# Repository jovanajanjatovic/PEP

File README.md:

## Set štampanih ploča namenjenih za učenje elektronike

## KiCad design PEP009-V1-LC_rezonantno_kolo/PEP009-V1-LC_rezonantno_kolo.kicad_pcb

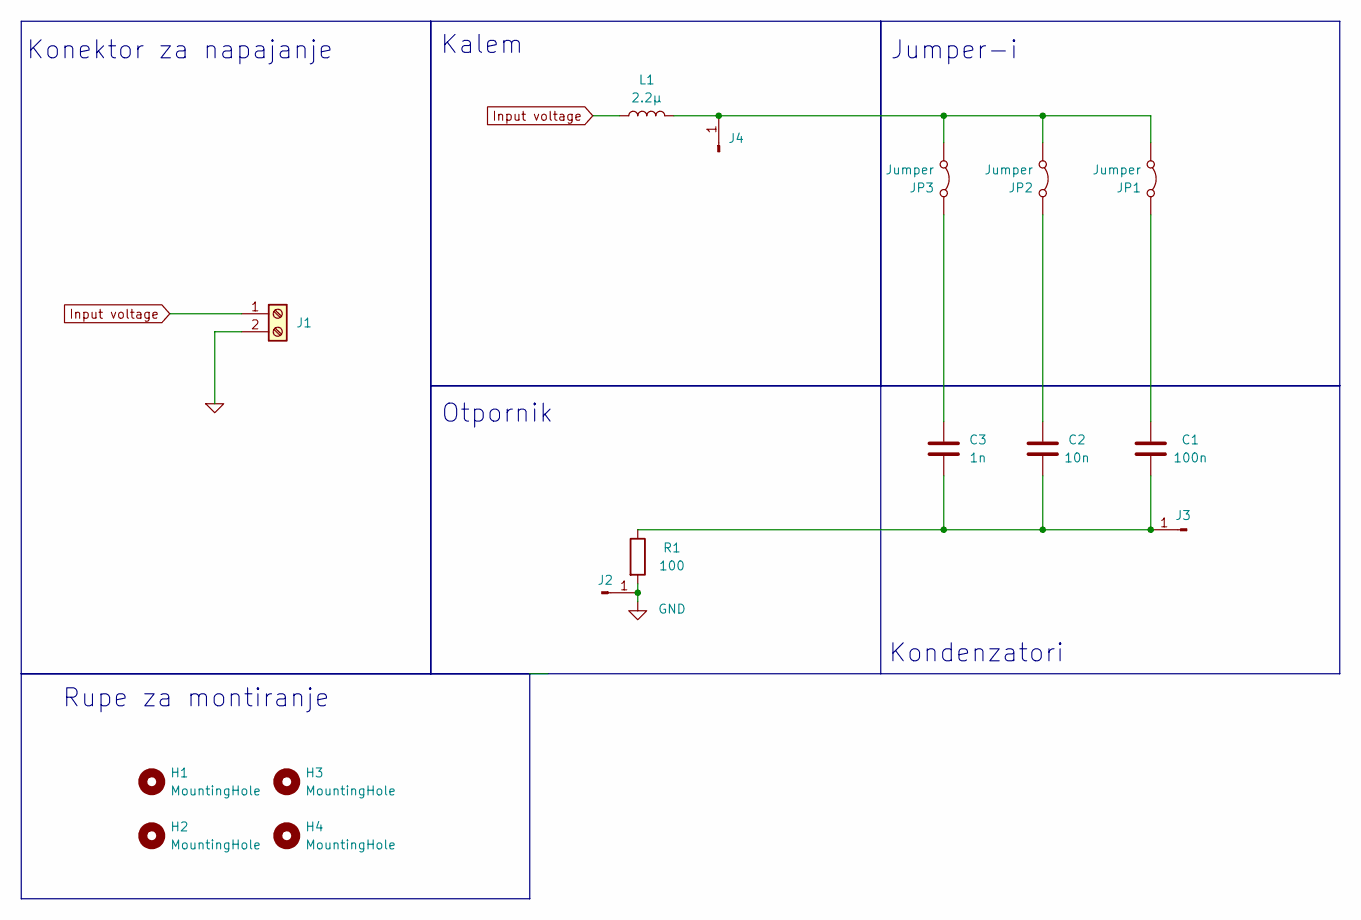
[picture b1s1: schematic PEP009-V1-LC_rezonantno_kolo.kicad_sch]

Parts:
C1: 100n; C_1206_3216Metric; LCSC C24497
C2: 10n; C_1206_3216Metric; LCSC C1846
C3: 1n; C_1206_3216Metric; LCSC C9196
H1, H2, H3, H4: MountingHole; MountingHole_3.2mm_M3_ISO14580_Pad_TopBottom
J1: Screw_Terminal_01x02; TerminalBlock_Phoenix_MKDS-1,5-2-5.08_1x02_P5.08mm_Horizont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
J2, J3, J4: Conn_01x01_Pin; PinHeader_1x01_P2.54mm_Vertical
JP1, JP2, JP3: Jumper; PinHeader_1x02_P2.54mm_Vertical
L1: 2.2µ; L_0805_2012Metric; LCSC C55755
R1: 100; R_smd; LCSC C17901

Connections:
0: J1.2
GND: J2.1, R1.2
Input voltage: J1.1, L1.1
unnamed: C1.2, C2.2, C3.2, J3.1, R1.1
unnamed: J4.1, JP1.1 (A), JP2.1 (A), JP3.1 (A), L1.2
unnamed: C1.1, JP1.2 (B)
unnamed: C2.1, JP2.2 (B)
unnamed: C3.1, JP3.2 (B)

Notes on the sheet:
Kondenzatori
Otpornik
Rupe za montiranje
Kalem
Konektor za napajanje
Jumper-i

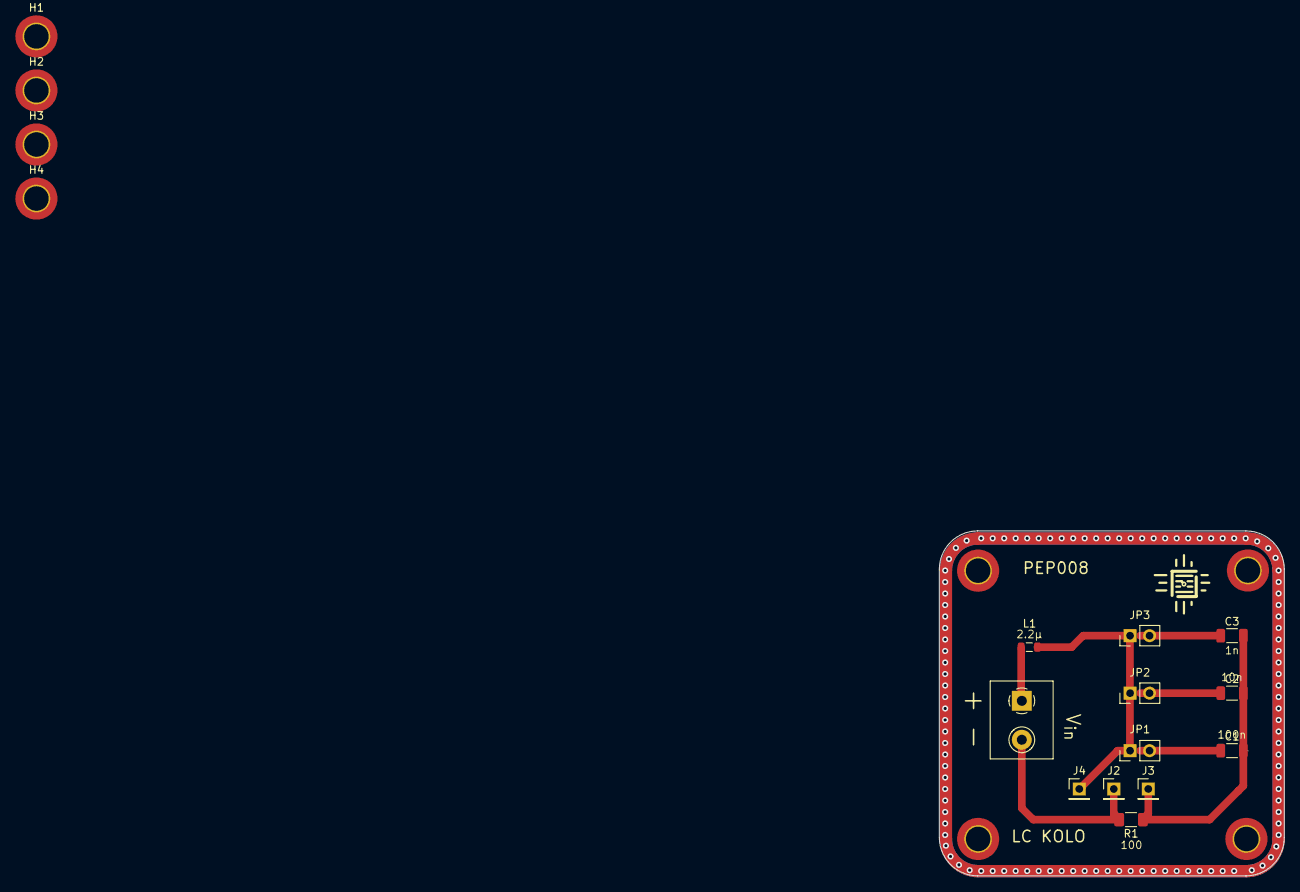
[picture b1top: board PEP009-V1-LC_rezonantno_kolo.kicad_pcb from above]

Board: 2 copper layers, 45.0 x 45.0 mm, 20 parts (0 on the bottom side), 7 nets.

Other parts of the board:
H1#2, H2#2, H3#2, H4#2: MountingHole; MountingHole_3.2mm_M3_ISO14580_Pad_TopBottom

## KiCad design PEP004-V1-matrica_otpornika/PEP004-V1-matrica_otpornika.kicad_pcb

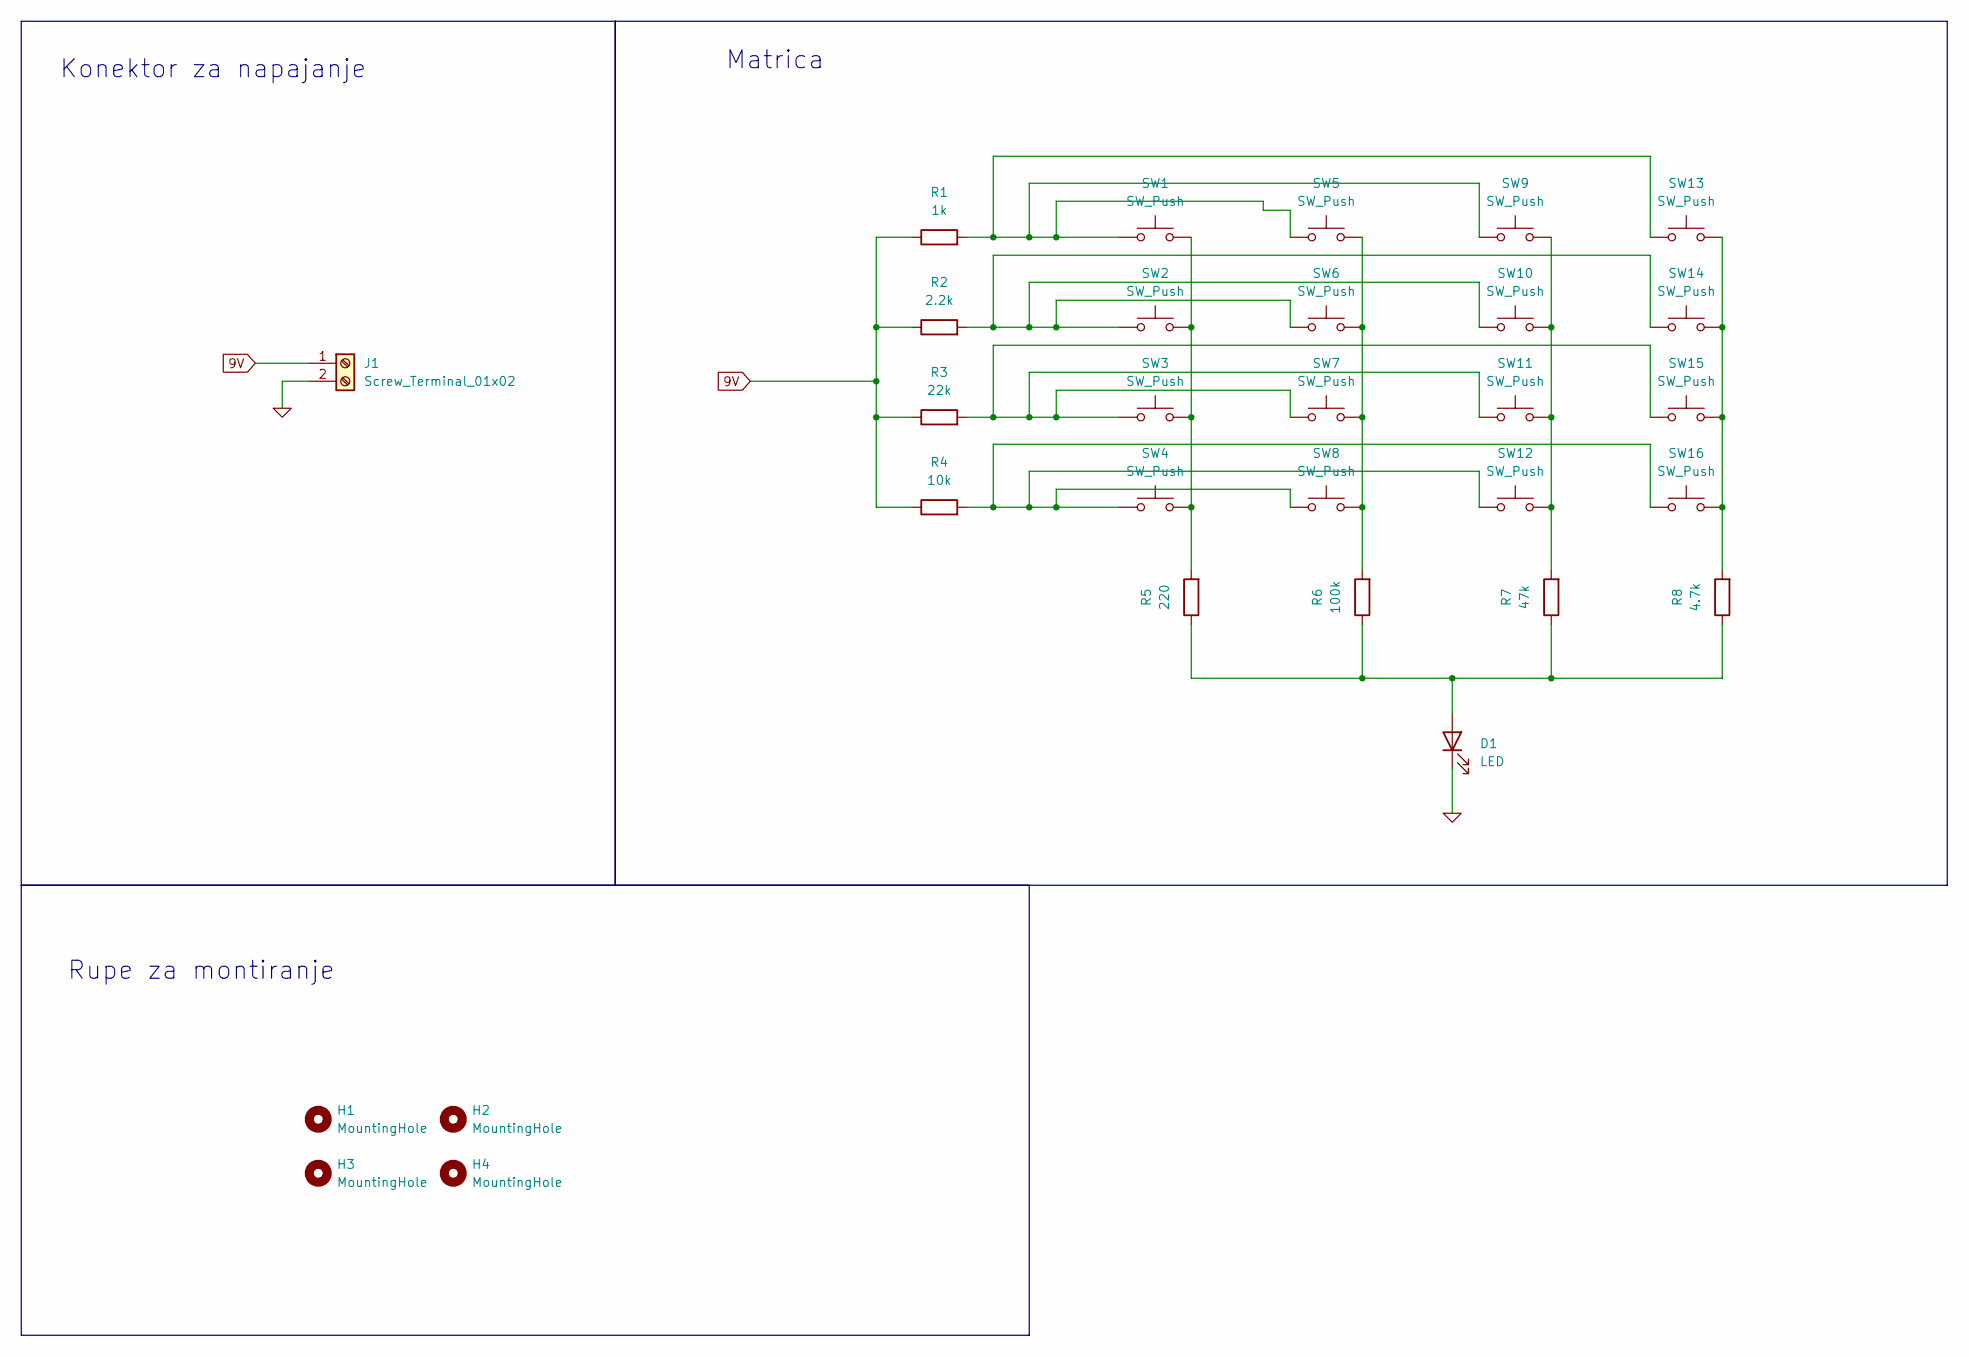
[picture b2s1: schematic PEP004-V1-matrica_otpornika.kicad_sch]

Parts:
D1: LED; LED_1206_3216Metric_Pad1.42x1.75mm_HandSolder
H1, H2, H3, H4: MountingHole; MountingHole_3.2mm_M3_ISO14580_Pad_TopBottom
J1: Screw_Terminal_01x02; TerminalBlock_Phoenix_MKDS-1,5-2-5.08_1x02_P5.08mm_Horizont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
R1: 1k; R_1206_3216Metric_Pad1.30x1.75mm_HandSolder
R2: 2.2k; R_1206_3216Metric_Pad1.30x1.75mm_HandSolder
R3: 22k; R_1206_3216Metric_Pad1.30x1.75mm_HandSolder
R4: 10k; R_1206_3216Metric_Pad1.30x1.75mm_HandSolder
R5: 220; R_1206_3216Metric_Pad1.30x1.75mm_HandSolder
R6: 100k; R_1206_3216Metric_Pad1.30x1.75mm_HandSolder
R7: 47k; R_1206_3216Metric_Pad1.30x1.75mm_HandSolder
R8: 4.7k; R_1206_3216Metric_Pad1.30x1.75mm_HandSolder
SW1, SW2, SW3, SW4, SW5, SW6, SW7, SW8, SW9, SW10, SW11, SW12, SW13, SW14, SW15, SW16: SW_Push; SW_PUSH_6mm_H4.3mm

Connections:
0: D1.1 (K), J1.2
9V: J1.1, R1.1, R2.1, R3.1, R4.1
unnamed: D1.2 (A), R5.1, R6.1, R7.1, R8.1
unnamed: R1.2, SW1.1, SW5.1, SW9.1, SW13.1
unnamed: R2.2, SW2.1, SW6.1, SW10.1, SW14.1
unnamed: R3.2, SW3.1, SW7.1, SW11.1, SW15.1
unnamed: R4.2, SW4.1, SW8.1, SW12.1, SW16.1
unnamed: R5.2, SW1.2, SW2.2, SW3.2, SW4.2
unnamed: R6.2, SW5.2, SW6.2, SW7.2, SW8.2
unnamed: R7.2, SW9.2, SW10.2, SW11.2, SW12.2
unnamed: R8.2, SW13.2, SW14.2, SW15.2, SW16.2

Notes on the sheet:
Rupe za montiranje
Konektor za napajanje
Matrica

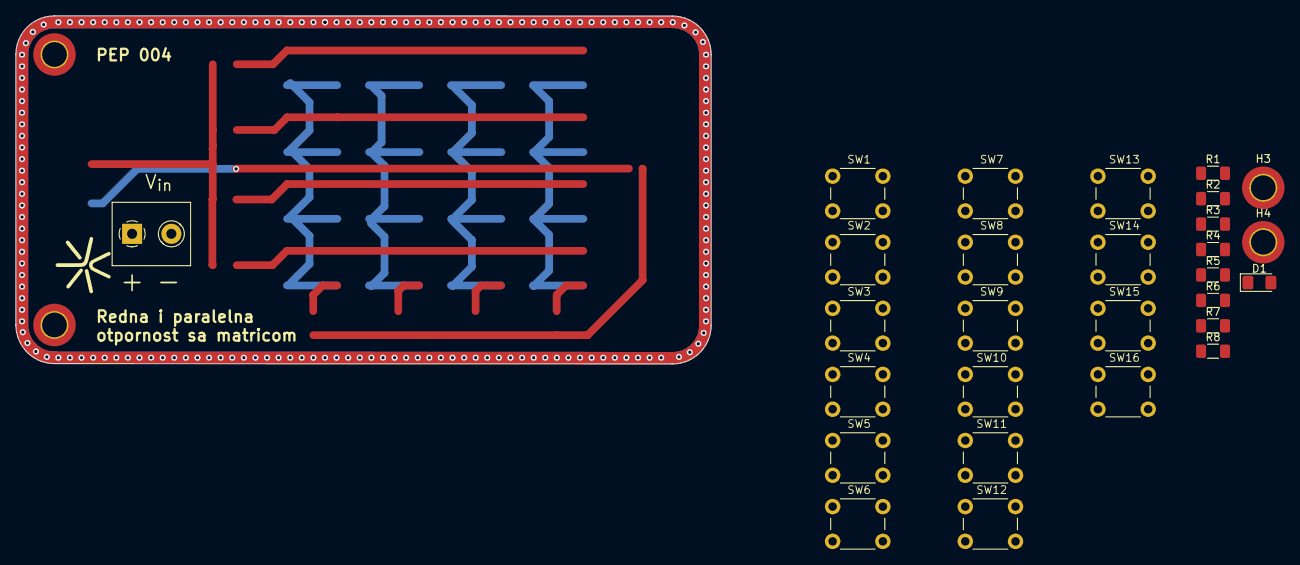
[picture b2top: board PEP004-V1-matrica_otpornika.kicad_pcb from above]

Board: 2 copper layers, 90.0 x 45.0 mm, 30 parts (0 on the bottom side), 11 nets.

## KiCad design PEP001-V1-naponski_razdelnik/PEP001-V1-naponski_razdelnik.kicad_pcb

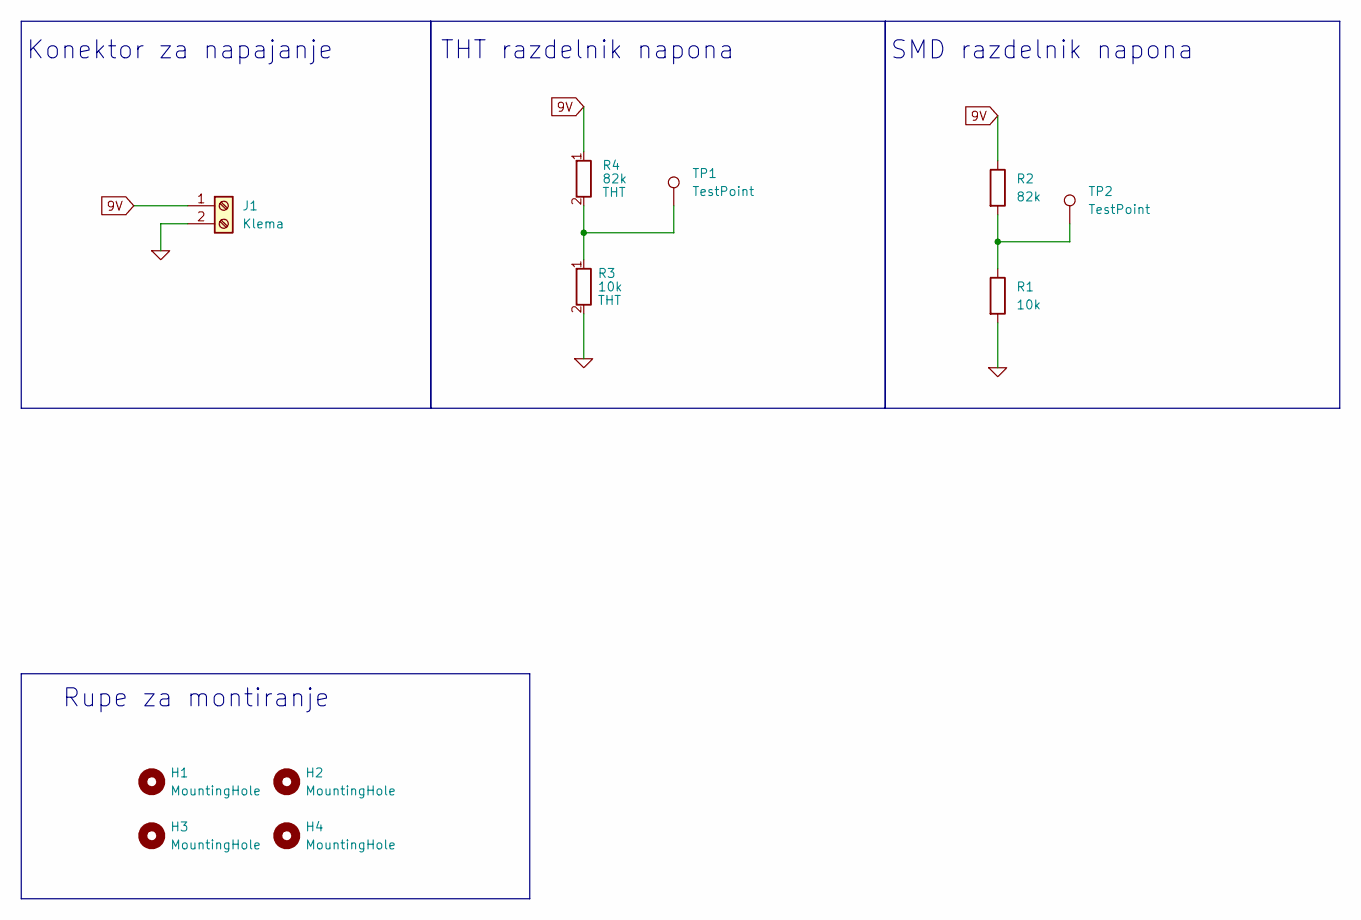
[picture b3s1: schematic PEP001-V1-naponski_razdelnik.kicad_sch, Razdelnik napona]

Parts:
H1, H2, H3, H4: MountingHole; MountingHole_3.2mm_M3_ISO14580_Pad_TopBottom
J1: Klema; TerminalBlock_Phoenix_MKDS-1,5-2-5.08_1x02_P5.08mm_Horizont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
R1: 10k; R_smd_1206; LCSC C17902
R2: 82k; R_smd_1206; LCSC C17979
R3: 10k; R_Axial_DIN0207_L6.3mm_D2.5mm_P15.24mm_Horizontal; LCSC C410695
R4: 82k; R_Axial_DIN0207_L6.3mm_D2.5mm_P15.24mm_Horizontal; LCSC C601724
TP1, TP2: TestPoint; TestPoint_Pad_D2.5mm

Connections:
0: J1.2, R1.2, R3.2
9V: J1.1, R2.1, R4.1
unnamed: R1.1, R2.2, TP2.1
unnamed: R3.1, R4.2, TP1.1

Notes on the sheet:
SMD razdelnik napona
Rupe za montiranje
Konektor za napajanje
THT razdelnik napona

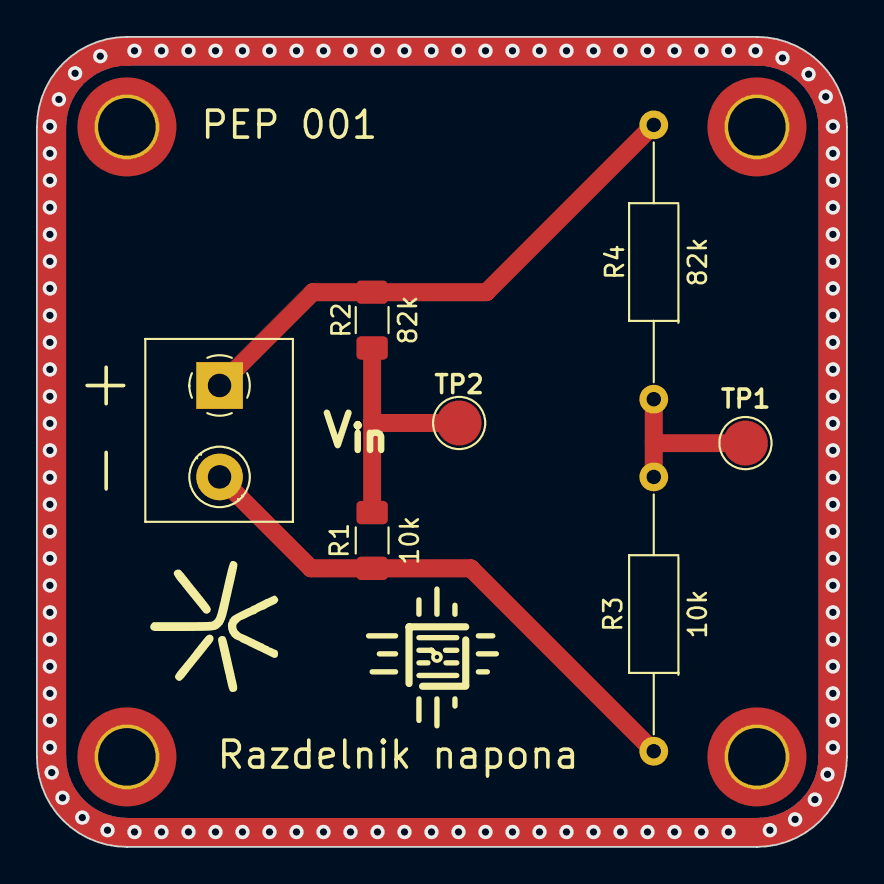
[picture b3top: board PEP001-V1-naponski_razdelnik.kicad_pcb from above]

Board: 2 copper layers, 45.0 x 45.0 mm, 11 parts (0 on the bottom side), 4 nets.

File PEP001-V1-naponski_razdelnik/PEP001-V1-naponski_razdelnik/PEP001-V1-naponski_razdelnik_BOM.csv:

"Comment","Designator","Footprint","LCSC Part Number"
"MountingHole,TestPoint","H1,H2,H3,H4,TP1,TP2","",""
"Screw_Terminal_01x02","J1","THT","C3018698"
"10k","R1","1206","C17902"
"82k","R2","1206","C17979"
"10k","R3","THT","C410695"
"82k","R4","THT","C601724"

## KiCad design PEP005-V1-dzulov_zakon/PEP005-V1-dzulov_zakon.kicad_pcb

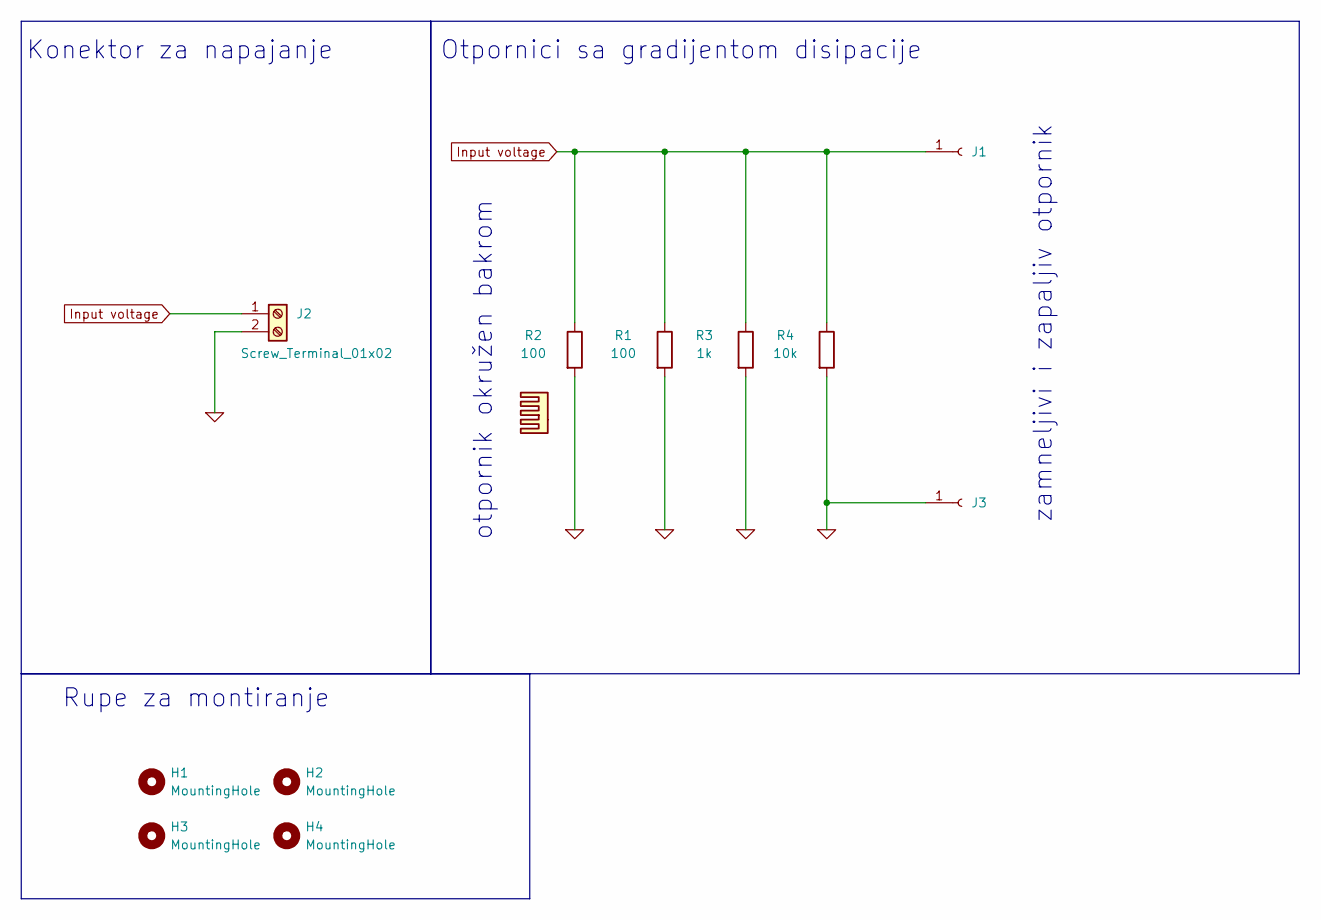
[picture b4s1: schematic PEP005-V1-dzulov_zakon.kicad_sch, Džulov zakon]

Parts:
H1, H2, H3, H4: MountingHole; MountingHole_3.2mm_M3_ISO14580_Pad_TopBottom
HS1: Heatsink
J1, J3: Conn_01x01_Socket; PinSocket_1x01_P2.54mm_Vertical
J2: Screw_Terminal_01x02; TerminalBlock_Phoenix_MKDS-1,5-2-5.08_1x02_P5.08mm_Horizont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; LCSC Part Number C3018698
R1, R2: 100; R_1206_3216Metric_Pad1.30x1.75mm_HandSolder; LCSC Part Number C17900
R3: 1k; R_1206_3216Metric_Pad1.30x1.75mm_HandSolder; LCSC Part Number C17900
R4: 10k; R_1206_3216Metric_Pad1.30x1.75mm_HandSolder; LCSC Part Number C17900

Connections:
0: J2.2, J3.1, R1.2, R2.2, R3.2, R4.2
Input voltage: J1.1, J2.1, R1.1, R2.1, R3.1, R4.1

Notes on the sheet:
zamneljivi i zapaljiv otpornik
Rupe za montiranje
otpornik okružen bakrom
Konektor za napajanje
Otpornici sa gradijentom disipacije

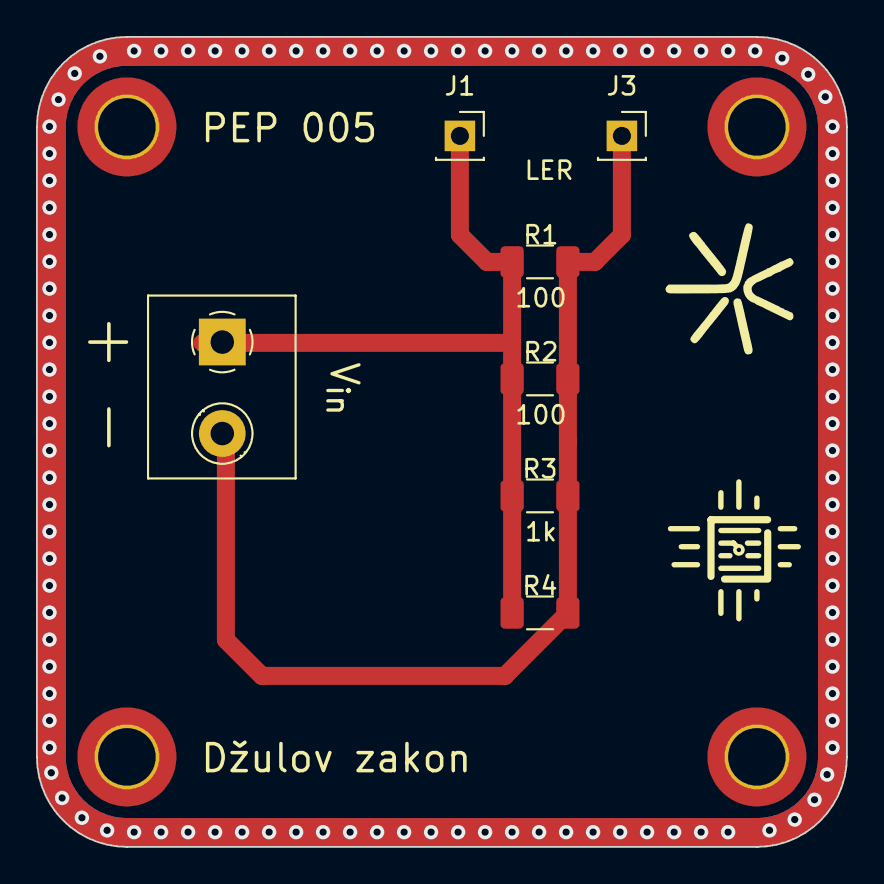
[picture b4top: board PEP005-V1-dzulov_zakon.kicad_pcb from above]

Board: 2 copper layers, 45.0 x 45.0 mm, 11 parts (0 on the bottom side), 2 nets.

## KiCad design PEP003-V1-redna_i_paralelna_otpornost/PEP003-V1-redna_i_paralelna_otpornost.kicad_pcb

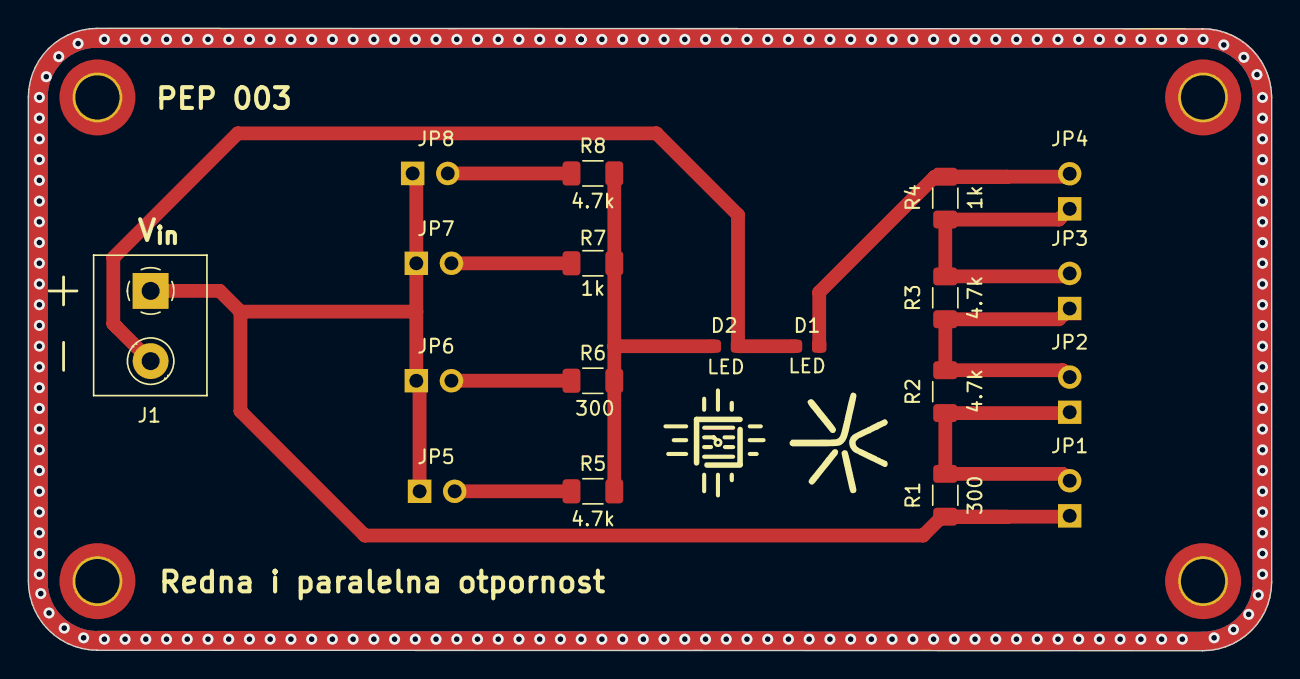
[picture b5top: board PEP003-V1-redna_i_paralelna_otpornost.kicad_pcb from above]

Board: 2 copper layers, 90.0 x 45.0 mm, 23 parts (0 on the bottom side), 2 nets.

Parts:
D1, D2: LED; LED_0603_1608Metric_Pad1.05x0.95mm_HandSolder
H1, H2, H3, H4: MountingHole; MountingHole_3.2mm_M3_ISO14580_Pad_TopBottom
J1: Screw_Terminal_01x02; TerminalBlock_Phoenix_MKDS-1,5-2-5.08_1x02_P5.08mm_Horizont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
JP1, JP2, JP3, JP4, JP5, JP6, JP7, JP8: Jumper; PinHeader_1x02_P2.54mm_Vertical
R1, R6: 300; R_smd
R2, R3, R5, R8: 4.7k; R_smd
R4, R7: 1k; R_smd

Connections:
0: D1.1 (K), D2.1 (K), J1.2
9V: J1.1, JP1.1 (A), JP5.1 (A), JP6.1 (A), JP7.1 (A), JP8.1 (A), R1.1

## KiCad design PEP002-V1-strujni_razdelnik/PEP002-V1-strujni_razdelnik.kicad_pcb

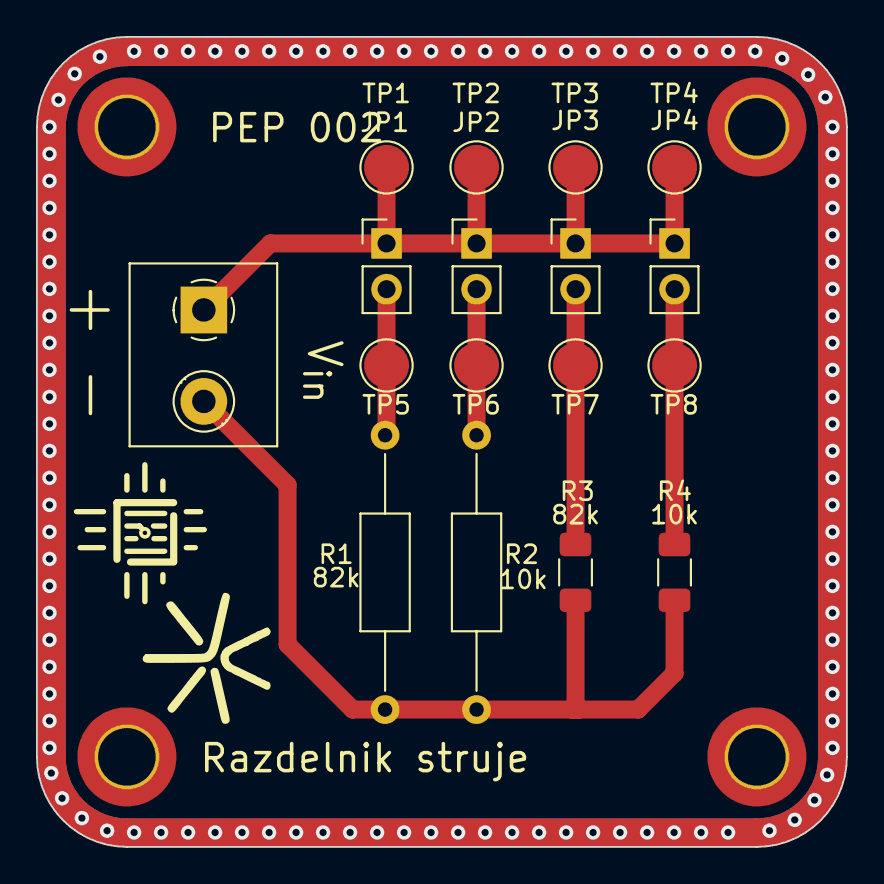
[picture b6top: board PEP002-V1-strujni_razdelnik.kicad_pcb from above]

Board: 2 copper layers, 45.0 x 45.0 mm, 21 parts (0 on the bottom side), 6 nets.

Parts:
H1, H2, H3, H4: MountingHole; MountingHole_3.2mm_M3_ISO14580_Pad_TopBottom
J1: Screw_Terminal_01x02; TerminalBlock_Phoenix_MKDS-1,5-2-5.08_1x02_P5.08mm_Horizont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
JP1, JP2, JP3, JP4: Jumper; PinHeader_1x02_P2.54mm_Vertical
R1: 82k; R_Axial_DIN0207_L6.3mm_D2.5mm_P15.24mm_Horizontal
R2: 10k; R_Axial_DIN0207_L6.3mm_D2.5mm_P15.24mm_Horizontal
R3: 82k; R_1206_3216Metric_Pad1.30x1.75mm_HandSolder
R4: 10k; R_1206_3216Metric_Pad1.30x1.75mm_HandSolder
TP1, TP2, TP3, TP4, TP5, TP6, TP7, TP8: TestPoint; TestPoint_Pad_D2.5mm

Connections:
0: J1.2, R1.1, R2.2, R3.2, R4.2
9V: J1.1, JP1.1 (A), JP2.1 (A), JP3.1 (A), JP4.1 (A), TP1.1, TP2.1, TP3.1, TP4.1
unnamed: JP1.2 (B), R1.2, TP5.1
unnamed: JP2.2 (B), R2.1, TP6.1
unnamed: JP3.2 (B), R3.1, TP7.1
unnamed: JP4.2 (B), R4.1, TP8.1

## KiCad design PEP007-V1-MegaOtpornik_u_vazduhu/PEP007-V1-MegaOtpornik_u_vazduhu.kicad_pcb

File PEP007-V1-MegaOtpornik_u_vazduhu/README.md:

# PEP 007 - MegaOtpornik u vazduhu

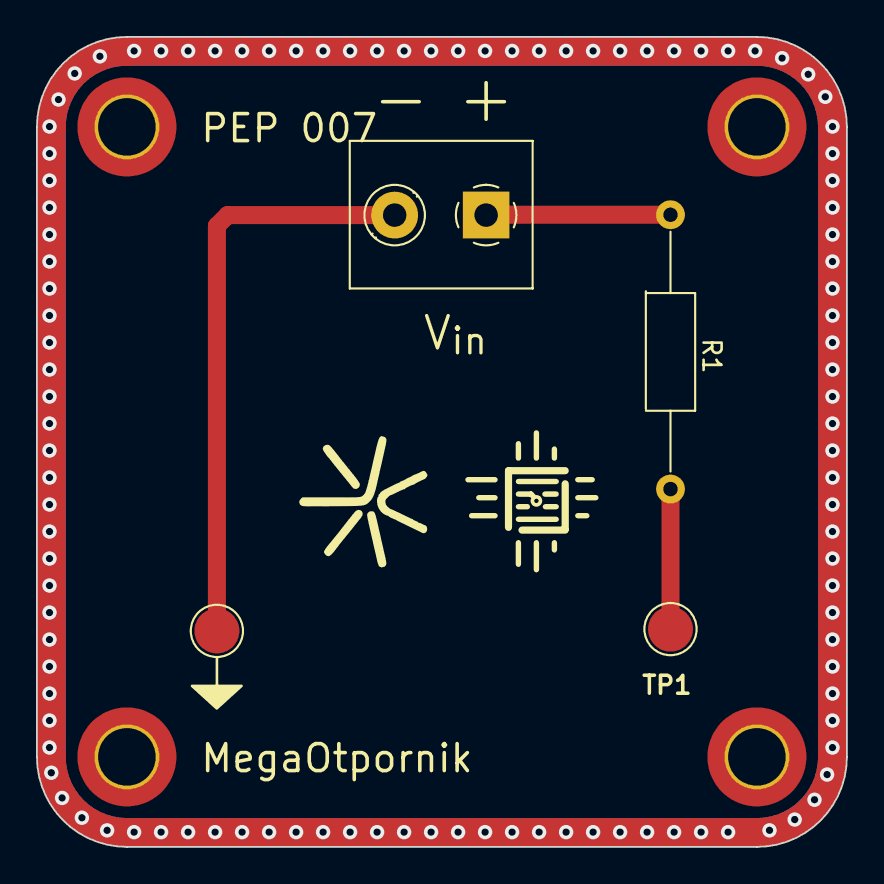
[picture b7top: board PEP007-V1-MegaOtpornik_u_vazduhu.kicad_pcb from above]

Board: 2 copper layers, 45.0 x 45.0 mm, 8 parts (0 on the bottom side), 3 nets.

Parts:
H1, H2, H3, H4: MountingHole; MountingHole_3.2mm_M3_ISO14580_Pad_TopBottom
J1: Klema; TerminalBlock_Phoenix_MKDS-1,5-2-5.08_1x02_P5.08mm_Horizont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
R1: 1Meg; R_Axial_DIN0207_L6.3mm_D2.5mm_P15.24mm_Horizontal
TP2: TP2; TestPoint_Pad_D2.5mm
TP2#2: TP1; TestPoint_Pad_D2.5mm

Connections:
0: J1.2, TP2.1
Input voltage: J1.1, R1.2
unnamed: R1.1, TP2#2.1

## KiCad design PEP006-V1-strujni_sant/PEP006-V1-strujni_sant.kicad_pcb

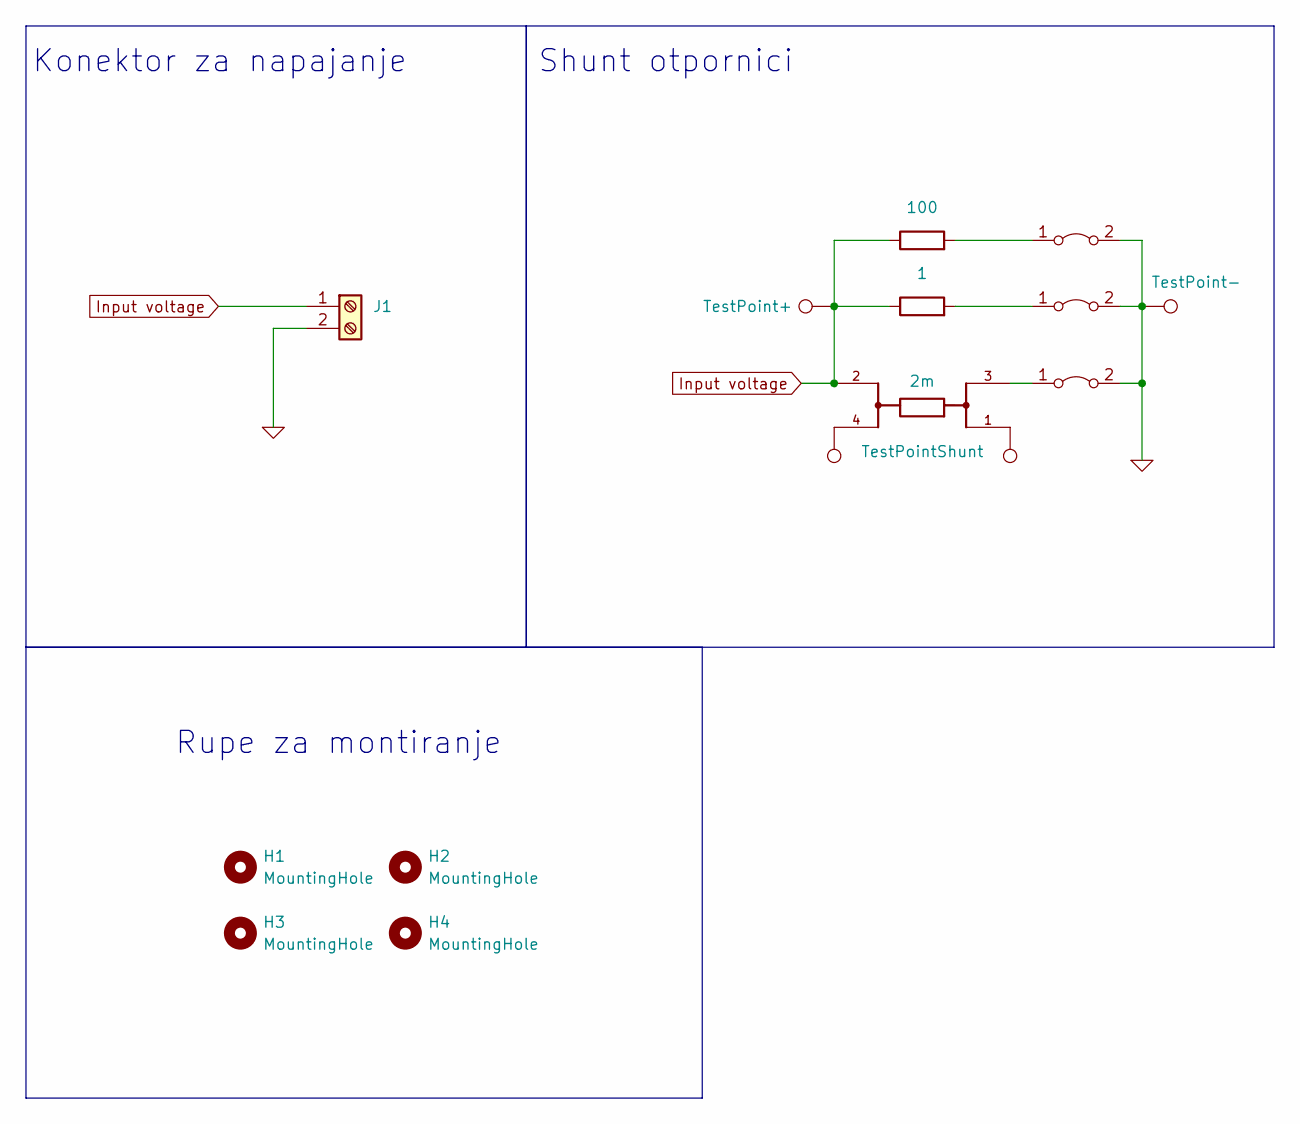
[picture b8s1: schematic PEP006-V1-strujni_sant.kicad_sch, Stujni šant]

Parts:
H1, H2, H3, H4: MountingHole; MountingHole_3.2mm_M3_ISO14580_Pad_TopBottom
J1: Screw_Terminal_01x02; TerminalBlock_Phoenix_MKDS-1,5-2-5.08_1x02_P5.08mm_Horizont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
JP1, JP2: Jumper; PinHeader_1x02_P2.54mm_Vertical
JP3: Jumper; PinHeader_1x02_P2.54mm_Vertical; LCSC C124375
R1: 2m; RES_WSK12161L000FEA; PARTREV 02-Aug-2024
R3: 100; R_1206_3216Metric_Pad1.30x1.75mm_HandSolder; LCSC C17900
R4: 1; R_1206_3216Metric_Pad1.30x1.75mm_HandSolder; LCSC C17902
TP3: TestPoint+; PinHeader_1x01_P2.54mm_Vertical
TP6, TP7: TestPointShunt; PinHeader_1x01_P2.54mm_Vertical
TP8: TestPoint-; PinHeader_1x01_P2.54mm_Vertical

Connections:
0: J1.2, JP1.2 (B), JP2.2 (B), JP3.2 (B), TP8.1
Input voltage: J1.1, R1.2, R3.1, R4.1, TP3.1
unnamed: JP1.1 (A), R3.2
unnamed: JP2.1 (A), R4.2
unnamed: JP3.1 (A), R1.3
unnamed: R1.1, TP7.1
unnamed: R1.4, TP6.1

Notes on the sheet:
Konektor za napajanje
Shunt otpornici
Rupe za montiranje

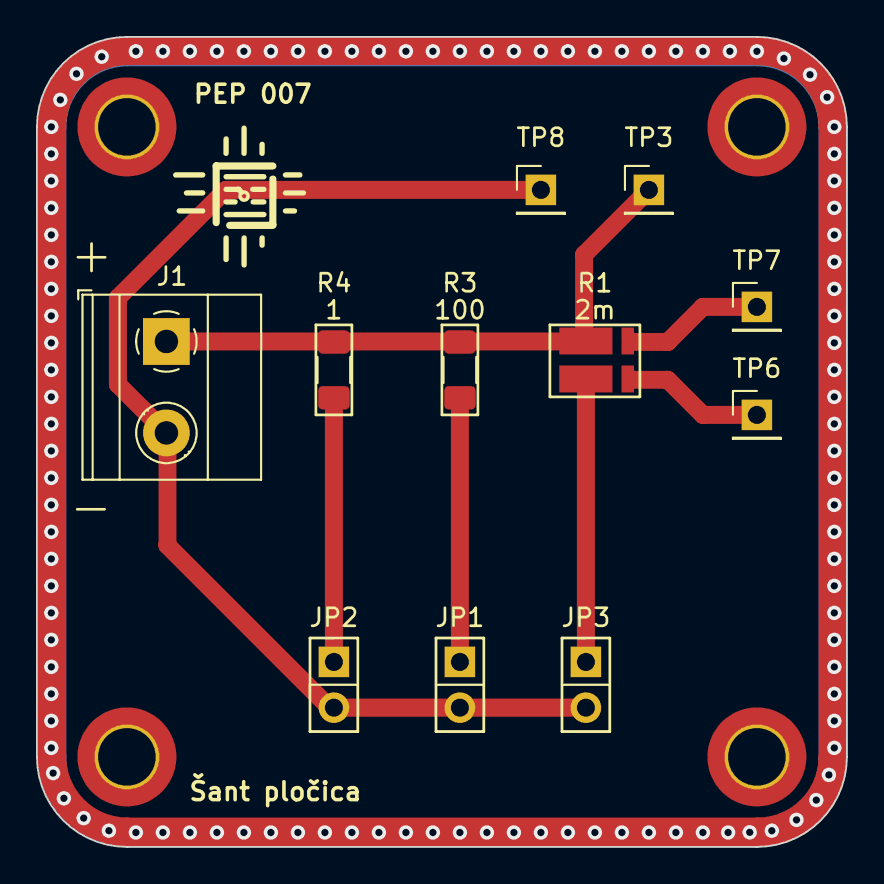
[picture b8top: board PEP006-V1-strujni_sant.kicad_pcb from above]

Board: 2 copper layers, 45.0 x 45.0 mm, 15 parts (0 on the bottom side), 7 nets.

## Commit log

2024-11-21 Init.
2024-11-22 Readmiss.
2024-11-22 three PEPsis.
2024-12-09 Added 006.
2024-12-09 Solder mask fix.
2024-12-10 006 rm, 001 img.
2024-12-10 Imgs.
2024-12-23 Updated template.
2025-02-02 Edge cuts fix on 45x45 template.
2025-02-02 New.
2025-02-02 julll.
2025-02-02 Džul update.
2025-02-03 New libs.
2025-02-03 Library updates.
2025-02-08 PEP008's init.
2025-02-11 PEP_libary update.
2025-02-11 PEP009 init.
2025-02-11 Templates updated.
2025-02-19 PEP008 update.
2025-02-19 PEP007 update.
2025-02-19 PEP008 rename
2025-02-19 PEP009 rename
2025-02-19 PEP006 rename.
2025-02-19 Shunt.
2025-02-19 Matrica i redna otpornost.
2025-02-19 Renaming el grande.
2025-02-19 Rename
2025-02-25 Template, library and PEP7 update.
2025-02-25 3, 4, 8.
2025-03-04 PEP006 and PEP009 update.
2025-03-04 PEP007 and lib update.
2025-03-04 PEP006 update.
2025-03-05 PEP006
2025-03-05 PEP003_in_progress.
2025-03-05 new template in progress.
2025-03-05 PEP003_update
2025-03-05 PEP004 and template 90 update.
2025-03-05 PEP007 final update, ready for production.
2025-03-05 PEP006 final commit, ready for production.
2025-03-05 PEP008 final commit, ready for production.
2025-03-05 PEP009 final commit, ready for production.
2025-03-05 PEP001 - Only LCSL linking left.
2025-03-05 PEP002 - Only LCSC linking left.
2025-03-06 PEP003 final commit, ready for production.
2025-03-06 PEP004 update.
2025-03-06 PEP001, PEP002 and PEP004 done.
2025-03-06 PEP010 final.
2025-03-06 PEP010 edge update.
2025-03-07 PEP006 final.
2025-03-07 PEP005 final.
2025-03-10 PEP lib update.
2025-03-12 Update 1,2,3,4,5,7, lib.
2025-03-31 Library moved, PEP004 placement needed.
2025-04-04 dodata šema kola
2025-04-05 dodate slike pločice
2025-04-24 svekuls
2025-04-25 Klema i kondenzatori zamenjeni sa onima iz PEP biblioteke. Naziv i broj plocice izmenjeni po standardnim pravilima
